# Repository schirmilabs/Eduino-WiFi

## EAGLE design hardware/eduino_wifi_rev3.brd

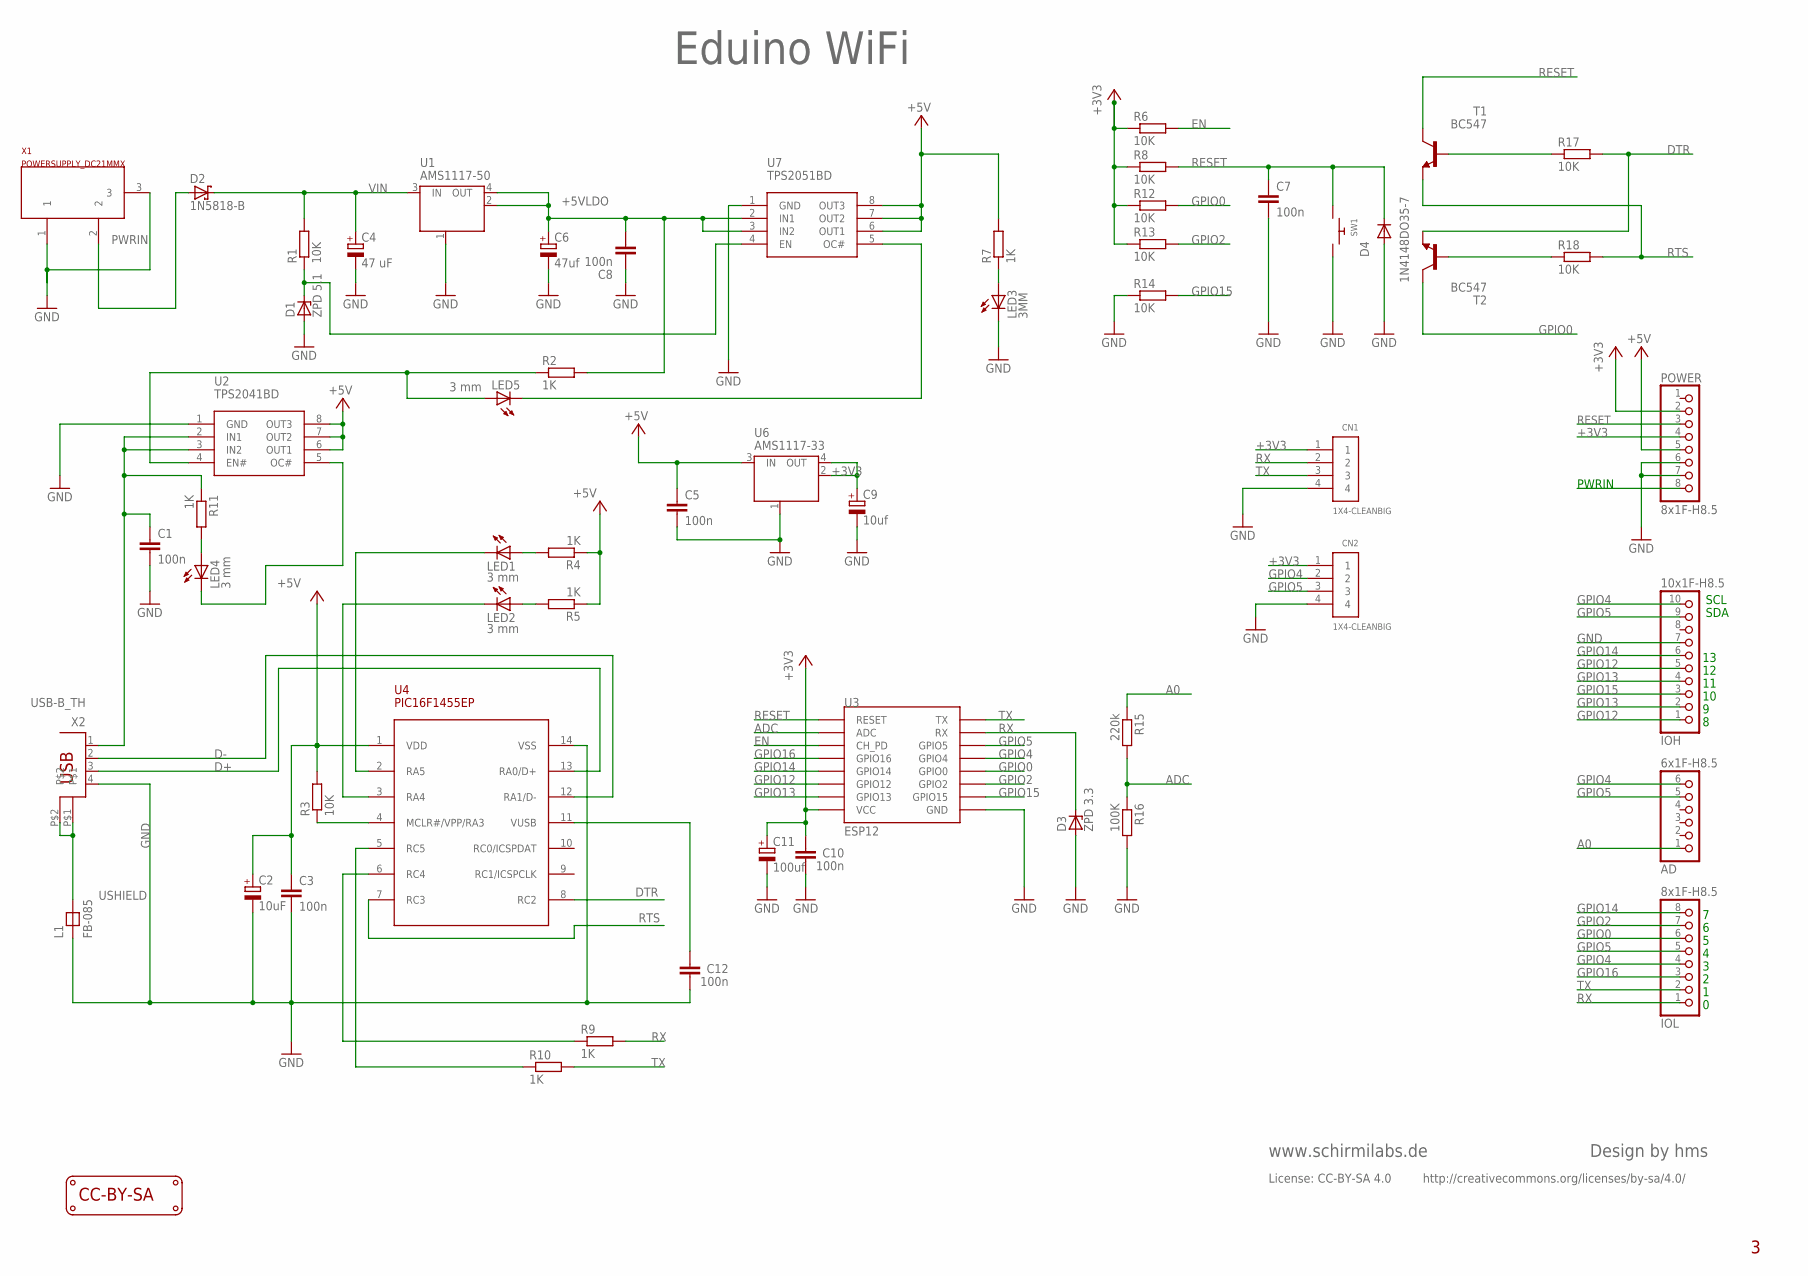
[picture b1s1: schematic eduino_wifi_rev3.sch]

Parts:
AD: 6x1F-H8.5; 1X06
C1, C3, C5, C7: 100n; C025-024X044
C2: 10uF; E2-5
C4: 47 uF; E2-5
C6: 47uf; E2-5
C8, C10, C12: 100n; C0.1PTH
C9: 10uf; E2-5
C11: 100uf; E2-5
CN1, CN2: 1X4-CLEANBIG; 1X04-CLEANBIG
D1: ZPD 5.1; DO35Z10
D2: 1N5818-B; DO41-7.6
D3: ZPD 3.3; DO35Z10
D4: 1N4148DO35-7; DO35-7
IOH: 10x1F-H8.5; 1X10
IOL: 8x1F-H8.5; 1X08
L1: FB-085
LED1, LED2, LED4, LED5: 3 mm; LED-3MM
LED3: 3MM; LED-3MM
LOGO1: LOGO_CC-BY-SA
POWER: 8x1F-H8.5; 1X08
R1, R6, R8, R12, R13, R14, R17, R18: 10K; RTH025W
R2, R4, R5, R7, R11: 1K; RTH025W
R3: 10K; 0207/10
R9, R10: 1K; 0207/10
R15: 220k; RTH025W
R16: 100K; RTH025W
SW1: SWITCH_PUSHBUTTONEVQ-PE; TACT_PANA-EVQ
T1, T2: BC547; TO92
U1: AMS1117-50; SOT223
U2: TPS2041BD; SOIC-8
U3: ESP12; ESP12-SMD
U4: PIC16F1455EP; DIL14
U6: AMS1117-33; SOT223
U7: TPS2051BD; SOIC-8
X1: POWERSUPPLY_DC21MMX; POWERSUPPLY_DC-21MM
X2: USB-B_TH; PN61729

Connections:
+3V3: C9.+, C10.2, C11.+, CN1.1, CN2.1, POWER.2, POWER.4, R6.1, R8.1, R12.1, R13.1, U3.VCC, U6.2 (OUT), U6.4 (OUT)
+5V: C2.+, C3.1, C5.1, POWER.5, R3.2, R4.1, R5.1, R7.2, U2.6 (OUT1), U2.7 (OUT2), U2.8 (OUT3), U4.1 (VDD), U6.3 (IN), U7.6 (OUT1), U7.7 (OUT2), U7.8 (OUT3)
+5VLDO: C6.+, C8.2, R2.2, U1.2 (OUT), U1.4 (OUT), U7.2 (IN1), U7.3 (IN2)
A0: AD.1, R15.1
ADC: R15.2, R16.1, U3.ADC
D+: U4.13 (RA0/D+), X2.3
D-: U4.12 (RA1/D-), X2.2
DTR: R17.2, T2.1 (E), U4.8 (RC2)
EN: R6.2, U3.CH_PD
GND: C1.2, C2.-, C3.2, C4.-, C5.2, C6.-, C7.2, C8.1, C9.-, C10.1, C11.-, C12.1, CN1.4, CN2.4, D1.A, D3.A, D4.A, IOH.7, L1.1, LED3.K (C), POWER.6, POWER.7, R14.1, R16.2, SW1.P$2, U1.1 (GND/ADJ), U2.1 (GND), U3.GND, U4.14 (VSS), U6.1 (GND/ADJ), U7.1 (GND), X1.1, X1.3, X2.4
GPIO0: IOL.6, R12.2, T2.3 (C), U3.GPIO0
GPIO2: IOL.7, R13.2, U3.GPIO2
GPIO4: AD.6, CN2.2, IOH.10, IOL.4, U3.GPIO4 (GPIO5)
GPIO5: AD.5, CN2.3, IOH.9, IOL.5, U3.GPIO5 (GPIO4)
GPIO12: IOH.1, IOH.5, U3.GPIO12
GPIO13: IOH.2, IOH.4, U3.GPIO13
GPIO14: IOH.6, IOL.8, U3.GPIO14
GPIO15: IOH.3, R14.2, U3.GPIO15
GPIO16: IOL.3, U3.GPIO16
M8RXD: R9.1, U4.6 (RC4)
M8TXD: R10.1, U4.5 (RC5)
unnamed: LED3.A, R7.1
unnamed: LED4.K (C), U2.5 (OC#)
unnamed: R3.1, U4.4 (MCLR#/VPP/RA3)
unnamed: LED1.K (C), U4.2 (RA5)
unnamed: LED2.K (C), U4.3 (RA4)
unnamed: LED1.A, R4.2
unnamed: LED2.A, R5.2
unnamed: C1.1, R11.1, U2.2 (IN1), U2.3 (IN2), X2.1
unnamed: D1.C, R1.1, U7.4 (EN)
unnamed: LED5.A, R2.1, U2.4 (EN#)
unnamed: R17.1, T1.2 (B)
unnamed: LED4.A, R11.2
unnamed: C12.2, U4.11 (VUSB)
unnamed: LED5.K (C), U7.5 (OC#)
unnamed: R18.1, T2.2 (B)
PWRIN: D2.A, POWER.8, X1.2
RESET: C7.1, D4.C, POWER.3, R8.2, SW1.P$1, T1.3 (C), U3.RESET
RTS: R18.2, T1.1 (E), U4.7 (RC3)
RX: CN1.2, D3.C, IOL.1, R9.2, U3.RXD0 (RX)
TX: CN1.3, IOL.2, R10.2, U3.TXD0 (TX)
USHIELD: L1.2, X2.P$1, X2.P$2
VIN: C4.+, D2.C, R1.2, U1.3 (IN)

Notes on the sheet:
Eduino WiFi
SDA
SCL
PWRIN
www.schirmilabs.de
License: CC-BY-SA 4.0
http://creativecommons.org/licenses/by-sa/4.0/
Design by hms

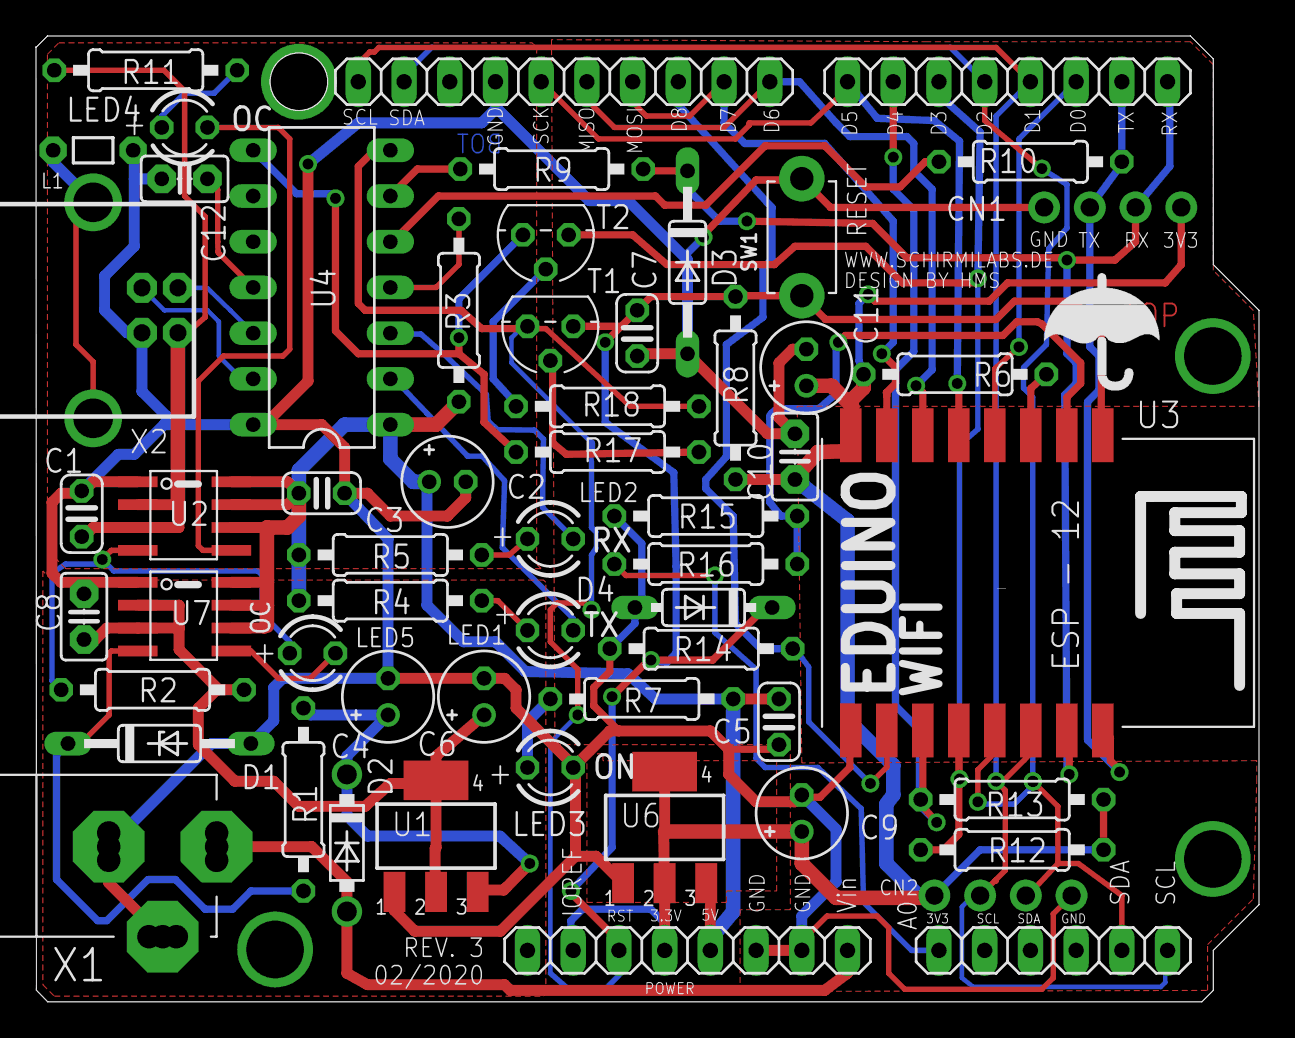
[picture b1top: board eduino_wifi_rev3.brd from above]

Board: 2 copper layers, 67.9 x 53.7 mm, 58 parts (1 on the bottom side), 43 nets.

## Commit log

2020-02-27 Added project files
2020-02-27 Add board picture
2020-02-29 Bugfix Assembly Manual
2020-03-01 Update Parts list
